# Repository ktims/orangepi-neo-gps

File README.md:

View this project on [CADLAB.io](https://cadlab.io/project/23107). 

# orangepi-neo-gps

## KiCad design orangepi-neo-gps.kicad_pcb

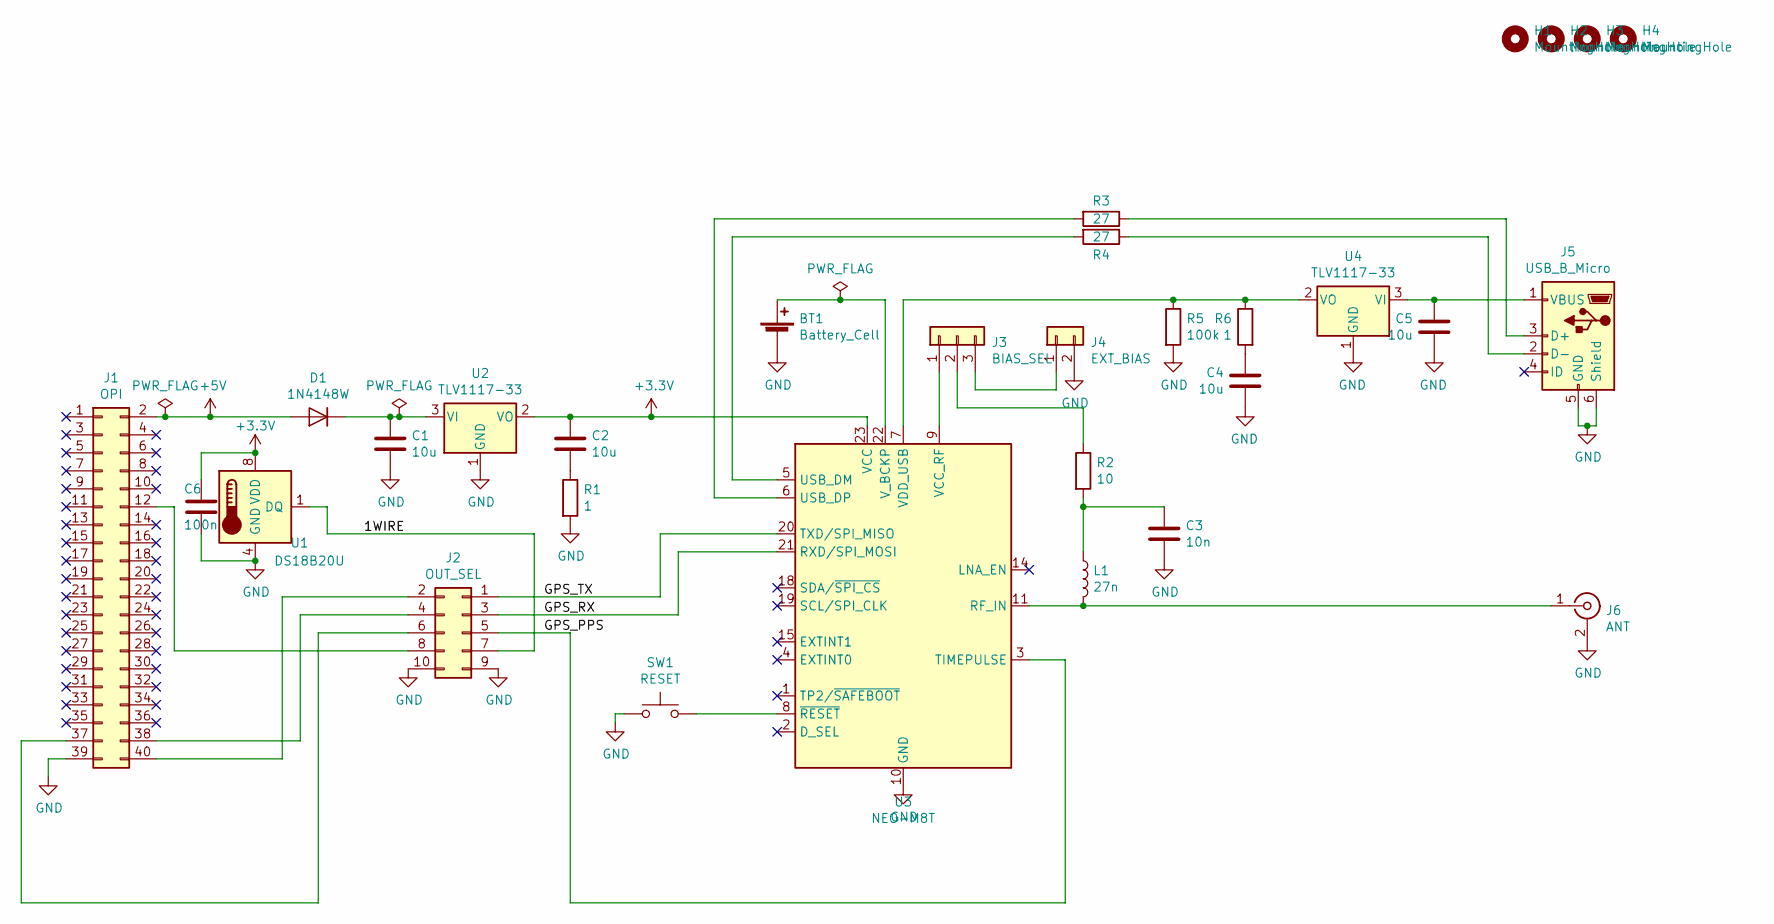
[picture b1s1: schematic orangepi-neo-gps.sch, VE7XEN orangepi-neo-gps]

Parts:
BT1: Battery_Cell; BatteryHolder_Keystone_1060_1x2032
C1, C2, C4, C5: 10u; C_1206_3216Metric_Pad1.42x1.75mm_HandSolder
C3: 10n; C_0805_2012Metric_Pad1.15x1.40mm_HandSolder
C6: 100n; C_0805_2012Metric_Pad1.15x1.40mm_HandSolder
D1: 1N4148W; D_SOD-123
H1, H2, H3, H4: MountingHole; MountingHole_3.2mm_M3_ISO7380_Pad
J1: OPI; PinSocket_2x20_P2.54mm_Vertical
J2: OUT_SEL; PinHeader_2x05_P2.54mm_Vertical
J3: BIAS_SEL; PinHeader_1x03_P2.54mm_Vertical
J4: EXT_BIAS; Molex_KK-254_AE-6410-02A_1x02_P2.54mm_Vertical
J5: USB_B_Micro; USB_Micro-B_Amphenol_10103594-0001LF_Horizontal
J6: ANT; SMA_Molex_73251-1153_EdgeMount_Horizontal
L1: 27n; L_0805_2012Metric_Pad1.15x1.40mm_HandSolder
R1, R6: 1; R_0805_2012Metric_Pad1.15x1.40mm_HandSolder
R2: 10; R_0805_2012Metric_Pad1.15x1.40mm_HandSolder
R3, R4: 27; R_0805_2012Metric_Pad1.15x1.40mm_HandSolder
R5: 100k; R_0805_2012Metric_Pad1.15x1.40mm_HandSolder
SW1: RESET; SW_Push_1P1T_NO_6x6mm_H9.5mm
U1: DS18B20U; MSOP-8_3x3mm_P0.65mm
U2, U4: TLV1117-33; SOT-223-3_TabPin2
U3: NEO-M8T; ublox_NEO

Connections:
+3V3: C2.1, C6.1, U1.8 (VDD), U2.2 (VO), U3.23 (VCC)
+5V: D1.2 (A), J1.2
/1WIRE: J2.7, U1.1 (DQ)
/GPS_PPS: J2.5, U3.3 (TIMEPULSE)
/GPS_RX: J2.3, U3.21 (RXD/SPI_MOSI)
/GPS_TX: J2.1, U3.20 (TXD/SPI_MISO)
GND: BT1.2 (-), C1.2, C3.2, C4.2, C5.2, C6.2, J1.39, J2.9, J2.10, J4.2, J5.5 (GND), J5.6 (Shield), J6.2 (Ext), R1.2, R5.2, SW1.1, U1.4 (GND), U2.1 (GND), U3.10 (GND), U3.12 (GND), U3.13 (GND), U3.24 (GND), U4.1 (GND)
unnamed: BT1.1 (+), U3.22 (V_BCKP)
unnamed: C1.1, D1.1 (K), U2.3 (VI)
unnamed: C2.2, R1.1
unnamed: C3.1, L1.1, R2.2
unnamed: C4.1, R6.2
unnamed: C5.1, J5.1 (VBUS), U4.3 (VI)
unnamed: J1.12, J2.8
unnamed: J1.37, J2.6
unnamed: J1.38, J2.4
unnamed: J1.40, J2.2
unnamed: J3.1, U3.9 (VCC_RF)
unnamed: J3.2, R2.1
unnamed: J3.3, J4.1
unnamed: J5.2 (D-), R4.1
unnamed: J5.3 (D+), R3.1
unnamed: J6.1 (In), L1.2, U3.11 (RF_IN)
unnamed: R3.2, U3.6 (USB_DP)
unnamed: R4.2, U3.5 (USB_DM)
unnamed: R5.1, R6.1, U3.7 (VDD_USB), U4.2 (VO)
unnamed: SW1.2, U3.8 (~RESET)

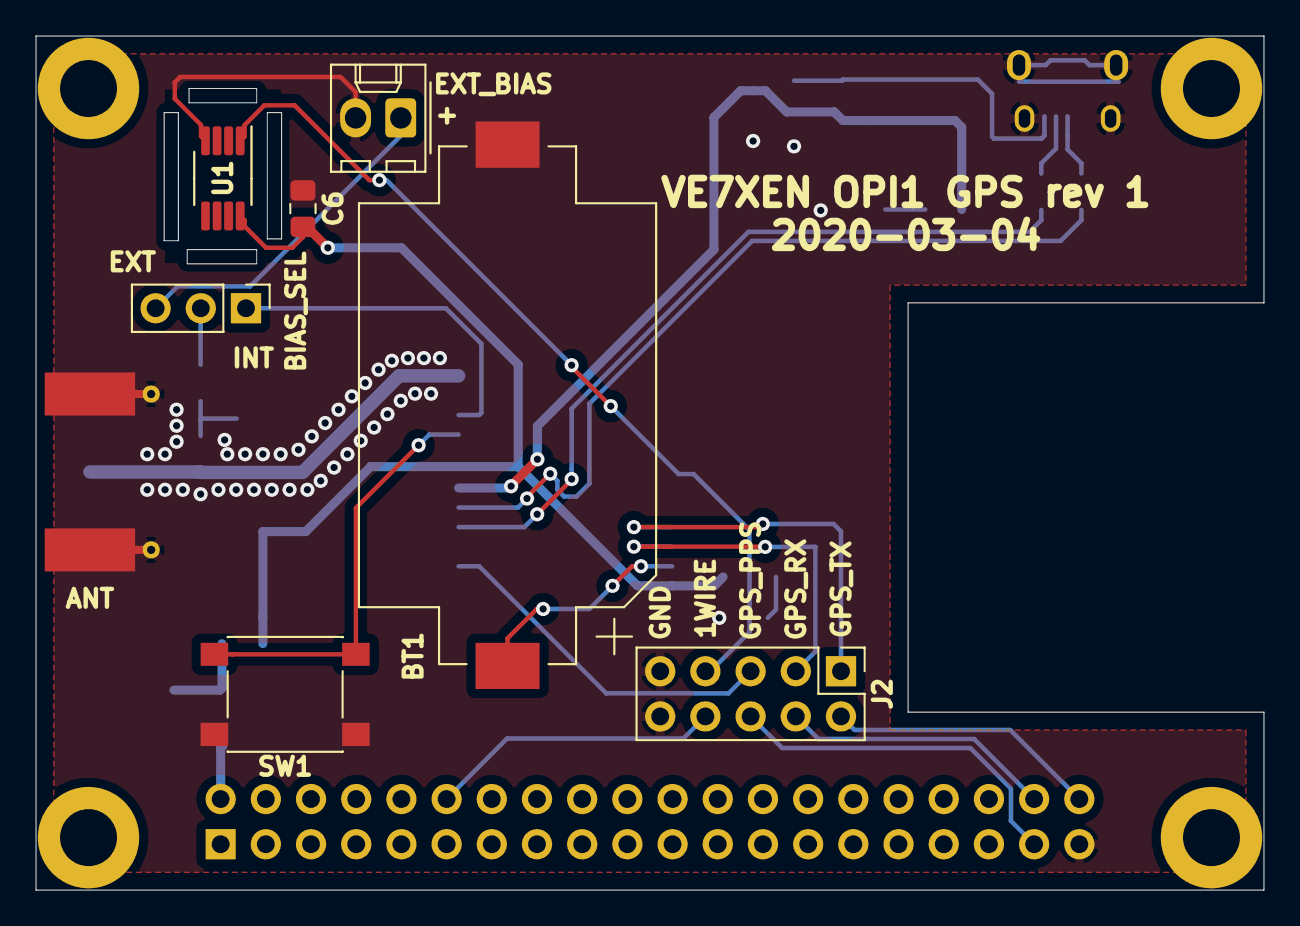
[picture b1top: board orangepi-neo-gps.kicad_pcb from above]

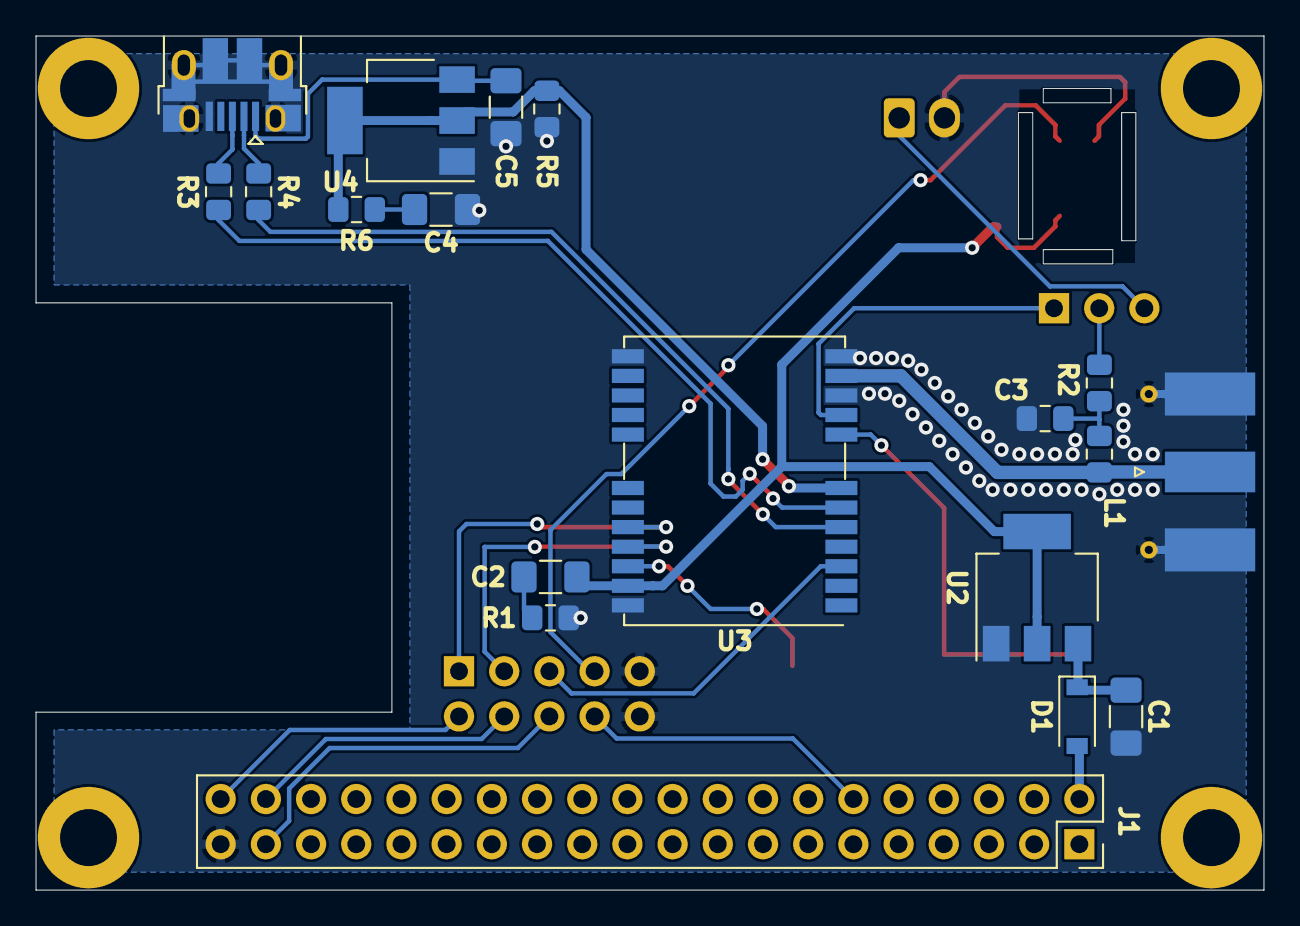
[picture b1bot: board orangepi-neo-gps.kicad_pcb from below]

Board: 2 copper layers, 69.0 x 48.0 mm, 30 parts (19 on the bottom side), 27 nets.

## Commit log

2020-03-06 Initial commit - rev 1 to fab
2020-03-06 Increase slot width for PCBWay constraints
2020-07-15 Backlink to CADLAB.io has been added.
